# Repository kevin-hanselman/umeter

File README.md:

UMeter
======
A Mass Storage/Data Logging device.

More information here: http://goo.gl/1UEr2P

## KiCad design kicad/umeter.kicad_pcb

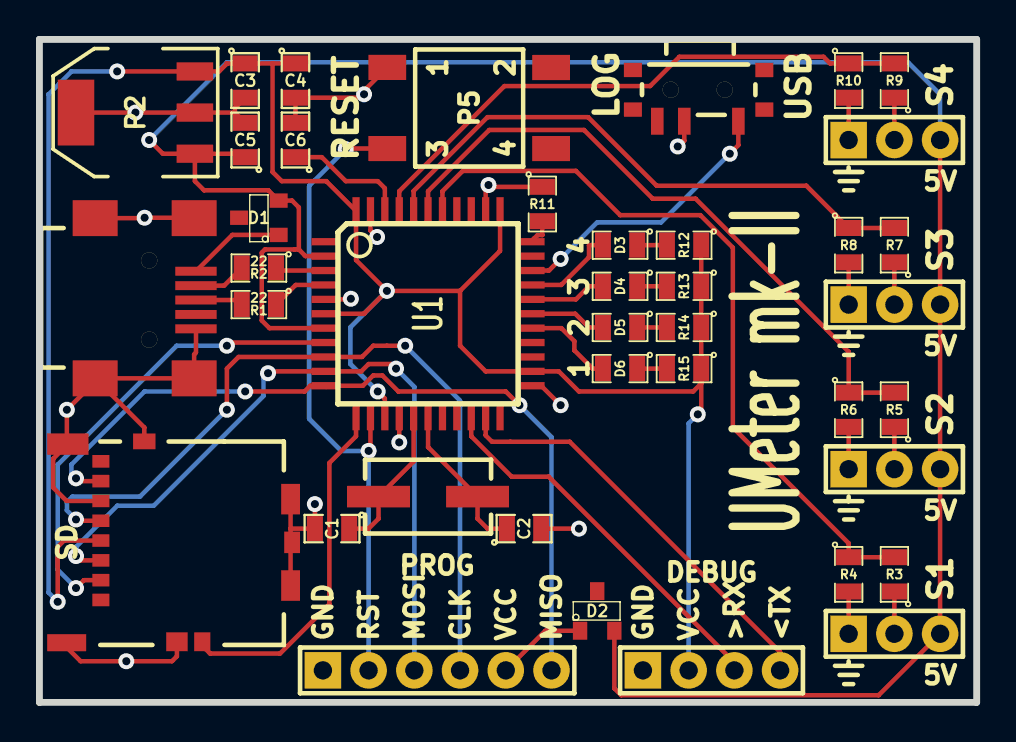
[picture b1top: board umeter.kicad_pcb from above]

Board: 2 copper layers, 52.1 x 36.8 mm, 40 parts (0 on the bottom side), 38 nets.

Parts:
C1, C2: 10pF; SM0805
C3, C5, C6: 1uF; SM0805
C4: 10uF; SM0805
D1, D2: DIODESCH; SOT23
D3, D4, D5, D6: LED; SM0805
J1: USB; USB_MINI_B_ED2992CT-ND
K1: S1; 3PIN_HEADER_100mil
K2: S2; 3PIN_HEADER_100mil
K3: S3; 3PIN_HEADER_100mil
K4: S4; 3PIN_HEADER_100mil
K5: MODE; SPARKFUN_COM-10860
P1: SD; MICROSD_MOLEX_5040771891
P2: MCP1825; SOT223
P3: DEBUG; 4PIN_HEADER_100mil
P4: PROG; 6PIN_HEADER_100mil
P5: RESET; SWITCH_FSM4JSMA
R1, R2: 22; SM0805
R3, R4, R5, R6, R7, R8, R9, R10: 100k; SM0805
R11, R12, R13, R14, R15: 1k; SM0805
U1: ATMEGA32U4; TQFP44
X1: 16MHz; CSM-3X

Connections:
+5V: C5.1, D1.2, D2.2, K1.3, K2.3, K3.3, K4.3, P2.1, U1.2, U1.7
/CS: P1.2, U1.8
/DETECT: P1.9, U1.12
/LED1: D6.2, U1.27
/LED2: D5.2, U1.28
/LED3: D4.2, U1.29
/LED4: D3.2, U1.30
/MISO: P1.7, P4.6, U1.11
/MODE: K5.1, U1.31
/MOSI: P1.3, P4.3, U1.10
/RESET: P4.2, P5.3, U1.13
/RX: P3.3, U1.20
/SCLK: P1.5, P4.4, U1.9
/SEN1: R3.2, R4.1, U1.38
/SEN2: R5.2, R6.1, U1.39
/SEN3: R7.2, R8.1, U1.40
/SEN4: R9.2, R10.1, U1.41
/TX: P3.4, U1.21
GND: C1.2, C2.2, C3.2, C4.2, C5.2, C6.2, J1.4, J1.5, J1.6, K1.1, K2.1, K3.1, K4.1, K5.2, P1.6, P1.10, P2.2, P2.4, P3.1, P4.1, P5.1, R4.2, R6.2, R8.2, R10.2, R11.1, U1.5, U1.15, U1.23, U1.35, U1.43
unnamed: K2.2, R5.1
unnamed: R11.2, U1.33
unnamed: R2.1, U1.3
unnamed: C1.1, U1.16, X1.1
unnamed: J1.2, R2.2
unnamed: J1.3, R1.2
unnamed: C6.1, U1.42
unnamed: R1.1, U1.4
unnamed: D1.1, J1.1
unnamed: D2.1, P4.5
unnamed: K3.2, R7.1
unnamed: K1.2, R3.1
unnamed: K4.2, R9.1
unnamed: C2.1, U1.17, X1.2
unnamed: D4.1, R13.2
unnamed: D6.1, R15.2
unnamed: D5.1, R14.2
unnamed: D3.1, R12.2
VCC: C3.1, C4.1, P1.4, P2.3, P3.2, R12.1, R13.1, R14.1, R15.1, U1.6, U1.14, U1.24, U1.34, U1.44

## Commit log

2012-11-18 All systems go
2012-11-27 Using older version of LUFA for stability
2012-12-10 changed main source file to UMeter.c
2012-12-12 updated project organization
2012-12-18 ini file parsing tested with integers and strings
2012-12-19 default ini values and basic value validation complete
2012-12-19 sensor sections added to umeter.ini
2012-12-20 added status LED for read/write in MassStorage and write in Datalogger modes
2013-04-18 First commit for PCBed UMeter
2013-05-18 started new project structure
2013-05-21 fixed includes for new directory structure
2013-05-21 builds successfully, fixed const/PROGMEM issue and more includes
2013-05-22 added kicad folder and umeter license file
2013-05-22 missed two component/module library files for kicad
2013-05-22 added footprint libraries to kicad dir
2013-05-27 fix nits
2013-05-28 added Readme
2013-05-28 redundant readme deleted
2015-06-30 add MIT license
